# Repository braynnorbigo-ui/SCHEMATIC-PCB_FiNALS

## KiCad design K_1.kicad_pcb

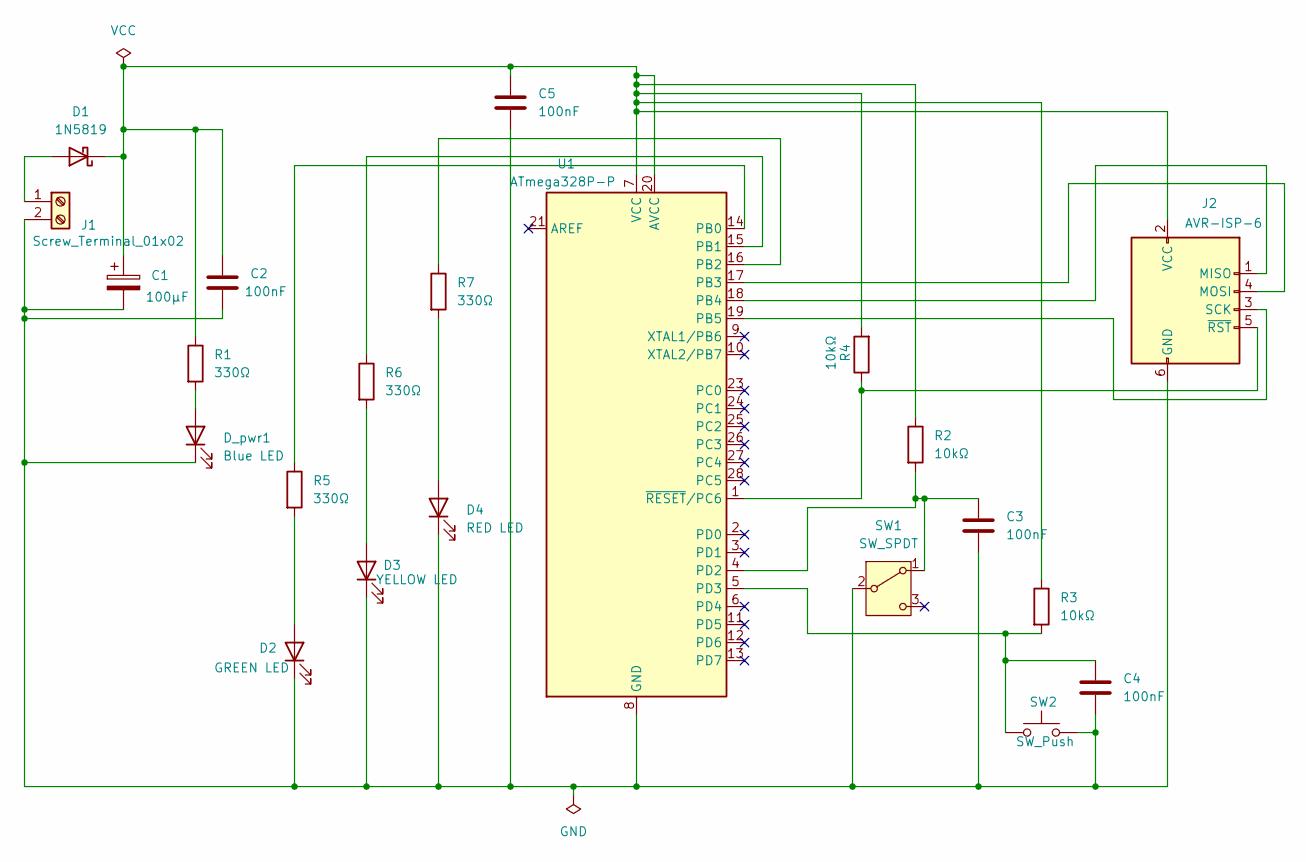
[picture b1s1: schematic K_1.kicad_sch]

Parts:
C1: 100µF; CP_Radial_D6.3mm_P2.50mm
C2, C3, C4, C5: 100nF; C_Disc_D5.0mm_W2.5mm_P5.00mm
D1: 1N5819; D_DO-41_SOD81_P10.16mm_Horizontal
D2: GREEN LED; LED_D5.0mm
D3: YELLOW LED; LED_D5.0mm
D4: RED LED; LED_D5.0mm
D_pwr1: Blue LED; LED_D5.0mm
J1: Screw_Terminal_01x02; TerminalBlock_Phoenix_MKDS-1,5-2_1x02_P5.00mm_Horizontal
J2: AVR-ISP-6; PinHeader_2x03_P2.54mm_Vertical
R1, R5, R6, R7: 330Ω; R_Axial_DIN0207_L6.3mm_D2.5mm_P10.16mm_Horizontal
R2, R3, R4: 10kΩ; R_Axial_DIN0207_L6.3mm_D2.5mm_P10.16mm_Horizontal
SW1: SW_SPDT; PinHeader_1x02_P2.54mm_Vertical
SW2: SW_Push; SW_PUSH_6mm
U1: ATmega328P-P; DIP-28_W7.62mm

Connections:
unnamed: D1.2 (A), J1.1
unnamed: C1.1, C2.1, C5.1, D1.1 (K), J2.2 (VCC), R1.1, R2.1, R3.1, R4.2, U1.7 (VCC), U1.20 (AVCC)
unnamed: D2.2 (A), R5.2
unnamed: C1.2, C2.2, C3.2, C4.2, C5.2, D2.1 (K), D3.1 (K), D4.1 (K), D_pwr1.1 (K), J1.2, J2.6 (GND), SW1.2 (B), SW2.2, U1.8 (GND), U1.22 (GND)
unnamed: D3.2 (A), R6.2
unnamed: D4.2 (A), R7.2
unnamed: D_pwr1.2 (A), R1.2
unnamed: J2.1 (MISO), U1.18 (PB4)
unnamed: J2.4 (MOSI), U1.17 (PB3)
unnamed: J2.3 (SCK), U1.19 (PB5)
unnamed: J2.5 (~RST), R4.1, U1.1 (~RESET/PC6)
unnamed: C3.1, R2.2, SW1.1 (A), U1.4 (PD2)
unnamed: R5.1, U1.14 (PB0)
unnamed: R6.1, U1.15 (PB1)
unnamed: R7.1, U1.16 (PB2)
unnamed: C4.1, R3.2, SW2.1, U1.5 (PD3)

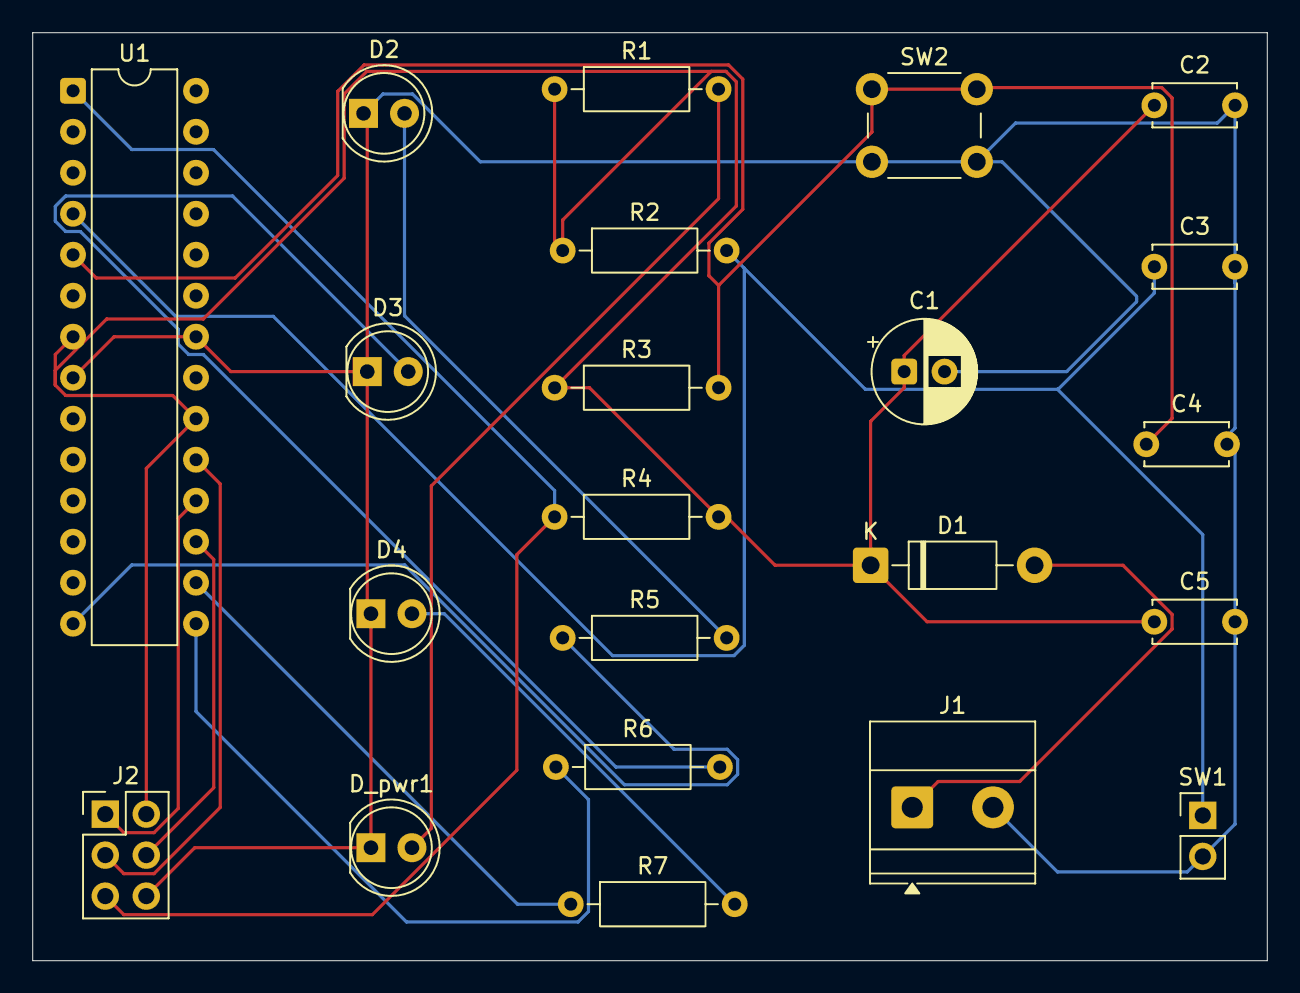
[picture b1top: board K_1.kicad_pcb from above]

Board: 2 copper layers, 76.5 x 57.5 mm, 22 parts (0 on the bottom side), 16 nets.
